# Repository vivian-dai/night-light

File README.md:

# night-light
I thought I should have some hardware projects on my Github so I decided to start with a fairly simple one. This is a night light that lights up when it's dark enough.

## 3D Render

## Components List
- 330 ohm resistor
- 100k ohm resistor
- BC547 (NPN transistor)
- photoresistor
- LED
- power source

## Creation Process
  
Above is the final schematic for this circuit. There are two parts to it, first is the right side which uses an NPN transistor as a switch. The left side is a voltage divider.  
### LED Math
These calculations were done to figure out the required resistance for the LED.
> Typically, the forward voltage of an LED is between 1.8 and 3.3 volts  
-- [Wikipedia](https://en.wikipedia.org/wiki/LED_circuit)

The specific LED I was using has a forward voltage drop of around 2V and needs about 10mA for it to function optimally. Using Ohm's law, we can calculate the required resistance.

$$
R = \frac{V_{power} - V_{forward}}{I} = \frac{6 - 2}{0.01} = 400
$$

I don't have a 400 ohm resistor. 330 is close enough (alternatively 470 would work too but I don't have that either).  
### Transistor as Switch
When looking at the [datasheet](https://www.sparkfun.com/datasheets/Components/BC546.pdf) for the transistor I used, it says the minimum voltage to turn the base on is 580mV. This means as long as a value greater than 580mV is passing through the base, there will be a current flowing from the collector to the emitter.
### Voltage Divider Math
The formula for voltage dividers can be found with a quick search.  

Above is an image from [Wikipedia](https://en.wikipedia.org/wiki/Voltage_divider). Wikipedia also gives us the formula for a voltage divider as 

$$
V_{out} = V_{in}\frac{R_2}{R_1 + R_2}
$$

In the schematics I drew up, $R_2$ of the voltage divider formula is the photoresistor and $R_1$ from the formula is the 100k resistor. This was determined by knowing the resistance of a photoresistor increases as it gets darker and when it's darker, we want more voltage. Since we want voltage and resistance to be porportional, the photoresistor should be $R_2$. I took a multimeter and measured the value of the photoresistor under normal light conditions. It was about 10k. We know $V_{in}$ is 6V and we want $V_{out}$ to be 0.58V so we now need to solve for the value of $R_1$.

$$V_{out} = V_{in}\frac{R_2}{R_1 + R_2}$$

$$0.58 = 6\frac{10}{10 + R_1}$$

$$5.8 + 0.58R_1 = 60$$

$$0.58R_1 = 54.2$$

$$R_1 \approx 93.4$$

I don't have a 93.4k resistor so I used an 100k resistor.

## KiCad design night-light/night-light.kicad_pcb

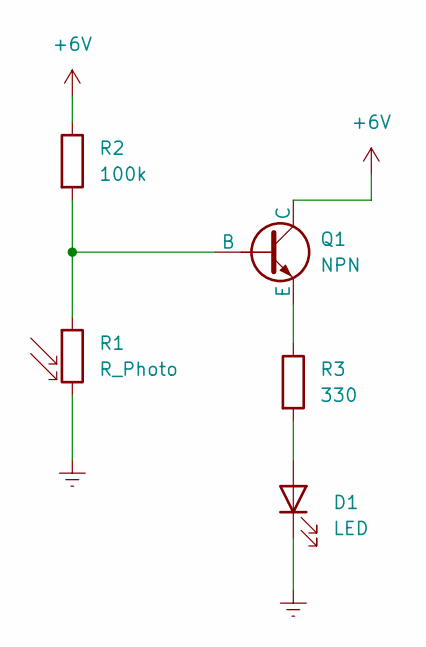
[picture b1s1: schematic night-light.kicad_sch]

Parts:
D1: LED; LED_D1.8mm_W3.3mm_H2.4mm
Q1: NPN; NEC_Molded_7x4x9mm
R1: R_Photo; R_LDR_4.9x4.2mm_P2.54mm_Vertical
R2: 100k; R_Axial_DIN0204_L3.6mm_D1.6mm_P5.08mm_Horizontal
R3: 330; R_Axial_DIN0204_L3.6mm_D1.6mm_P5.08mm_Horizontal

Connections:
+6V: Q1.1 (C), R2.1
Earth: D1.1 (K), R1.2
unnamed: D1.2 (A), R3.2
unnamed: Q1.2 (B), R1.1, R2.2
unnamed: Q1.3 (E), R3.1

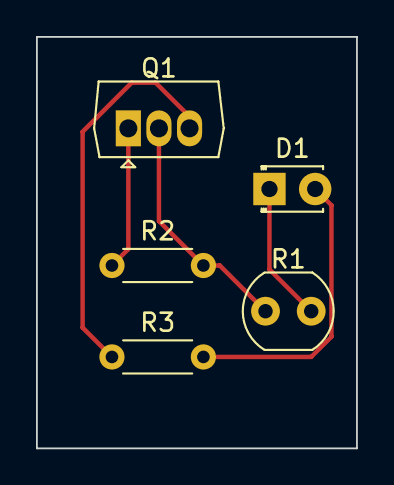
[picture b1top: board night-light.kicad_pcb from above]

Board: 2 copper layers, 17.8 x 22.9 mm, 5 parts (0 on the bottom side), 5 nets.

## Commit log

2023-11-30 create schematic and pcb files
2023-11-30 electronics math
2023-11-30 fix formatting
2023-12-05 fix math formating
2024-04-04 added images
